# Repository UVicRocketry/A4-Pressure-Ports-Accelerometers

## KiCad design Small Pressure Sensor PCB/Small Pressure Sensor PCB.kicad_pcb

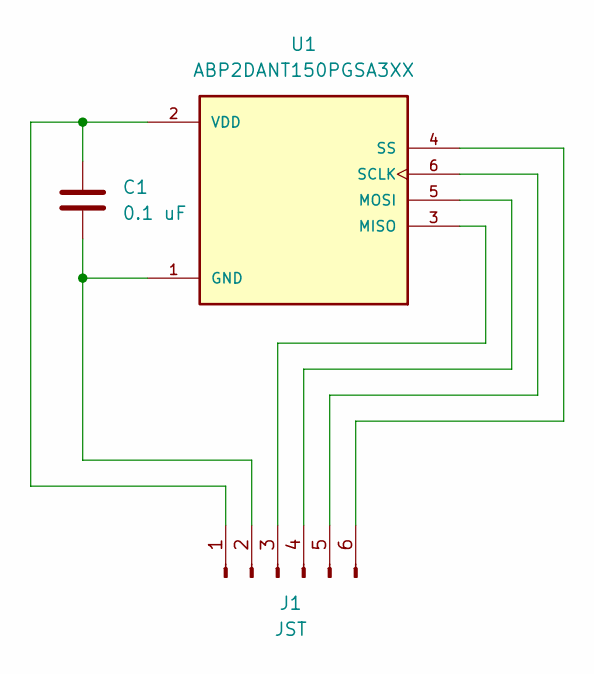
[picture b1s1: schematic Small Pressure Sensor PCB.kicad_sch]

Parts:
C1: 0.1 uF; C_0603_1608Metric_Pad1.08x0.95mm_HandSolder
J1: JST; JST_PH_S6B-PH-K_1x06_P2.00mm_Horizontal
U1: ABP2DANT150PGSA3XX; XDCR_ABP2DANT150PGSA3XX; MPN ABP2DANT150PGSA3XX; DigiKey_Part_Number 480-ABP2DANT150PGSA3XX-ND

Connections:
unnamed: C1.1, J1.1, U1.2 (VDD)
unnamed: C1.2, J1.2, U1.1 (GND)
unnamed: J1.3, U1.3 (MISO)
unnamed: J1.4, U1.5 (MOSI)
unnamed: J1.5, U1.6 (SCLK)
unnamed: J1.6, U1.4 (SS)

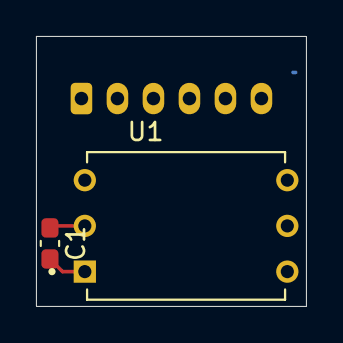
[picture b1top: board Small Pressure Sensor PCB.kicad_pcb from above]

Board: 2 copper layers, 15.0 x 15.0 mm, 3 parts (1 on the bottom side), 6 nets.
